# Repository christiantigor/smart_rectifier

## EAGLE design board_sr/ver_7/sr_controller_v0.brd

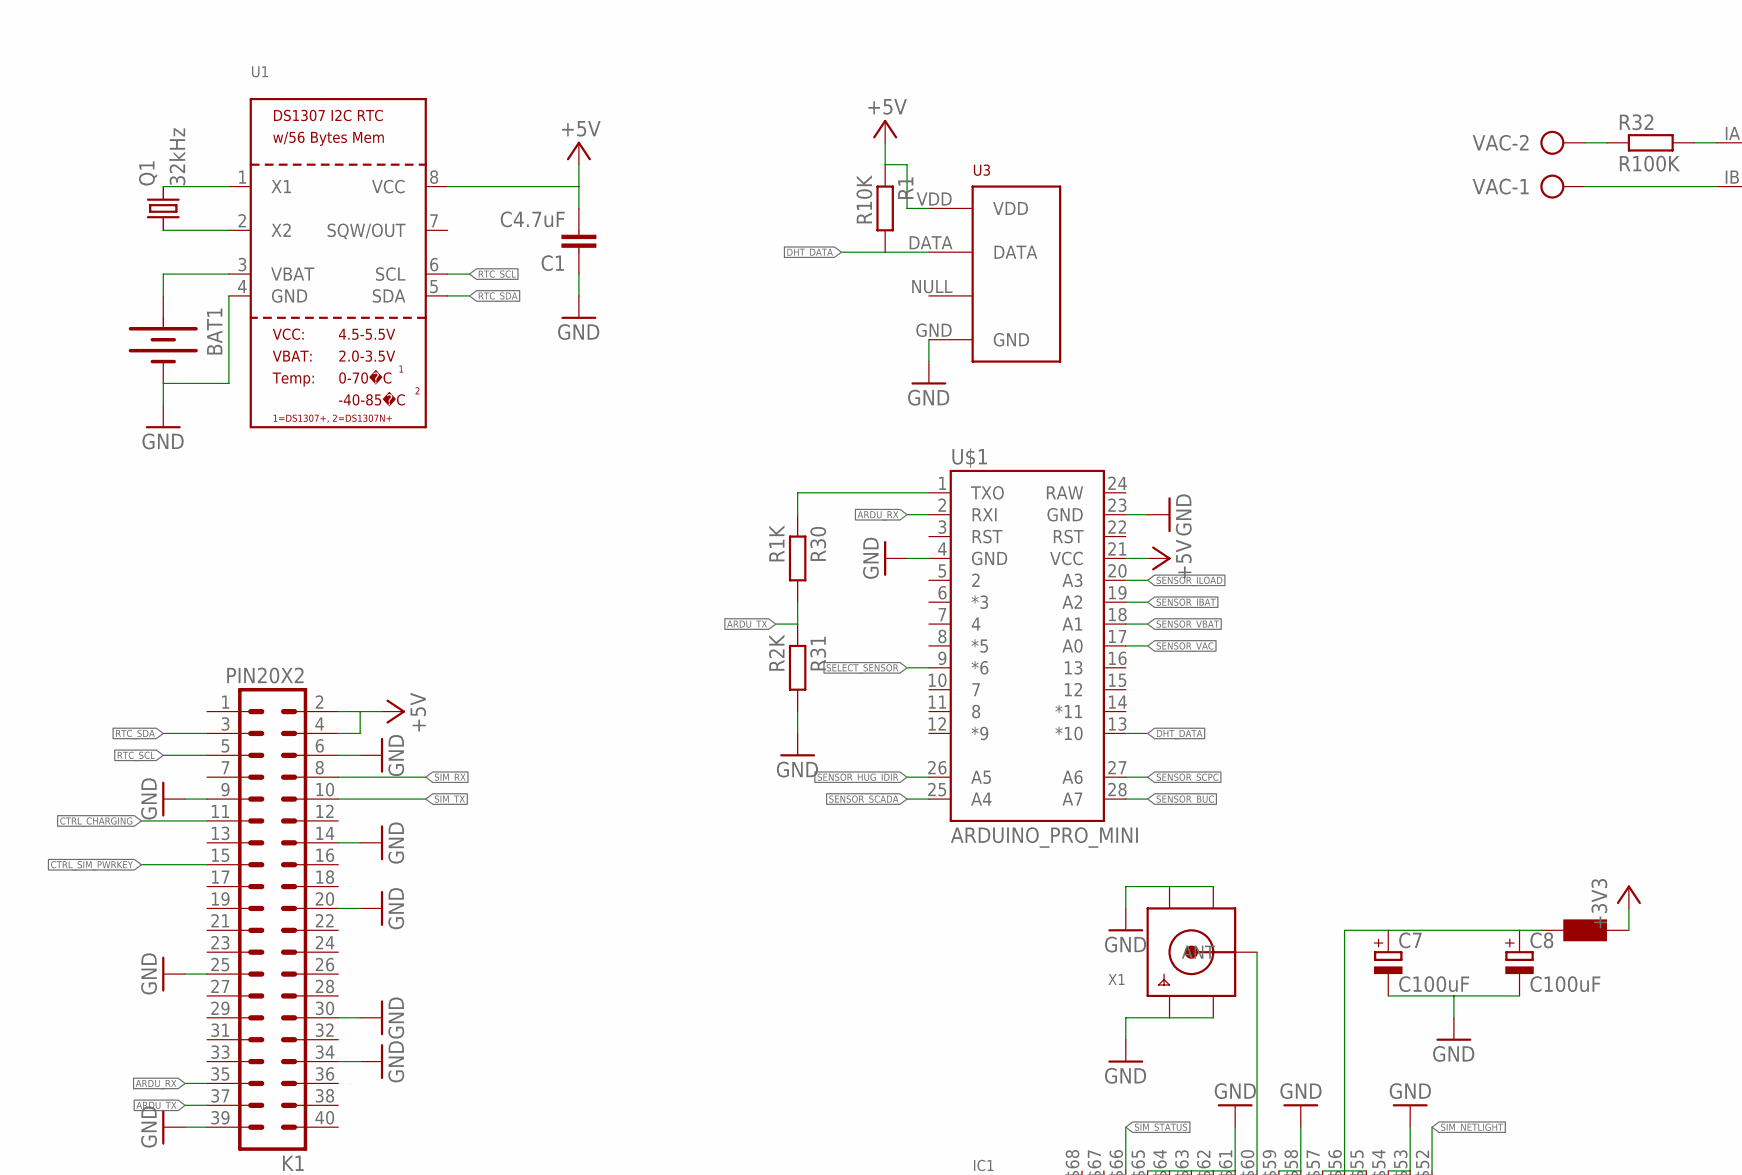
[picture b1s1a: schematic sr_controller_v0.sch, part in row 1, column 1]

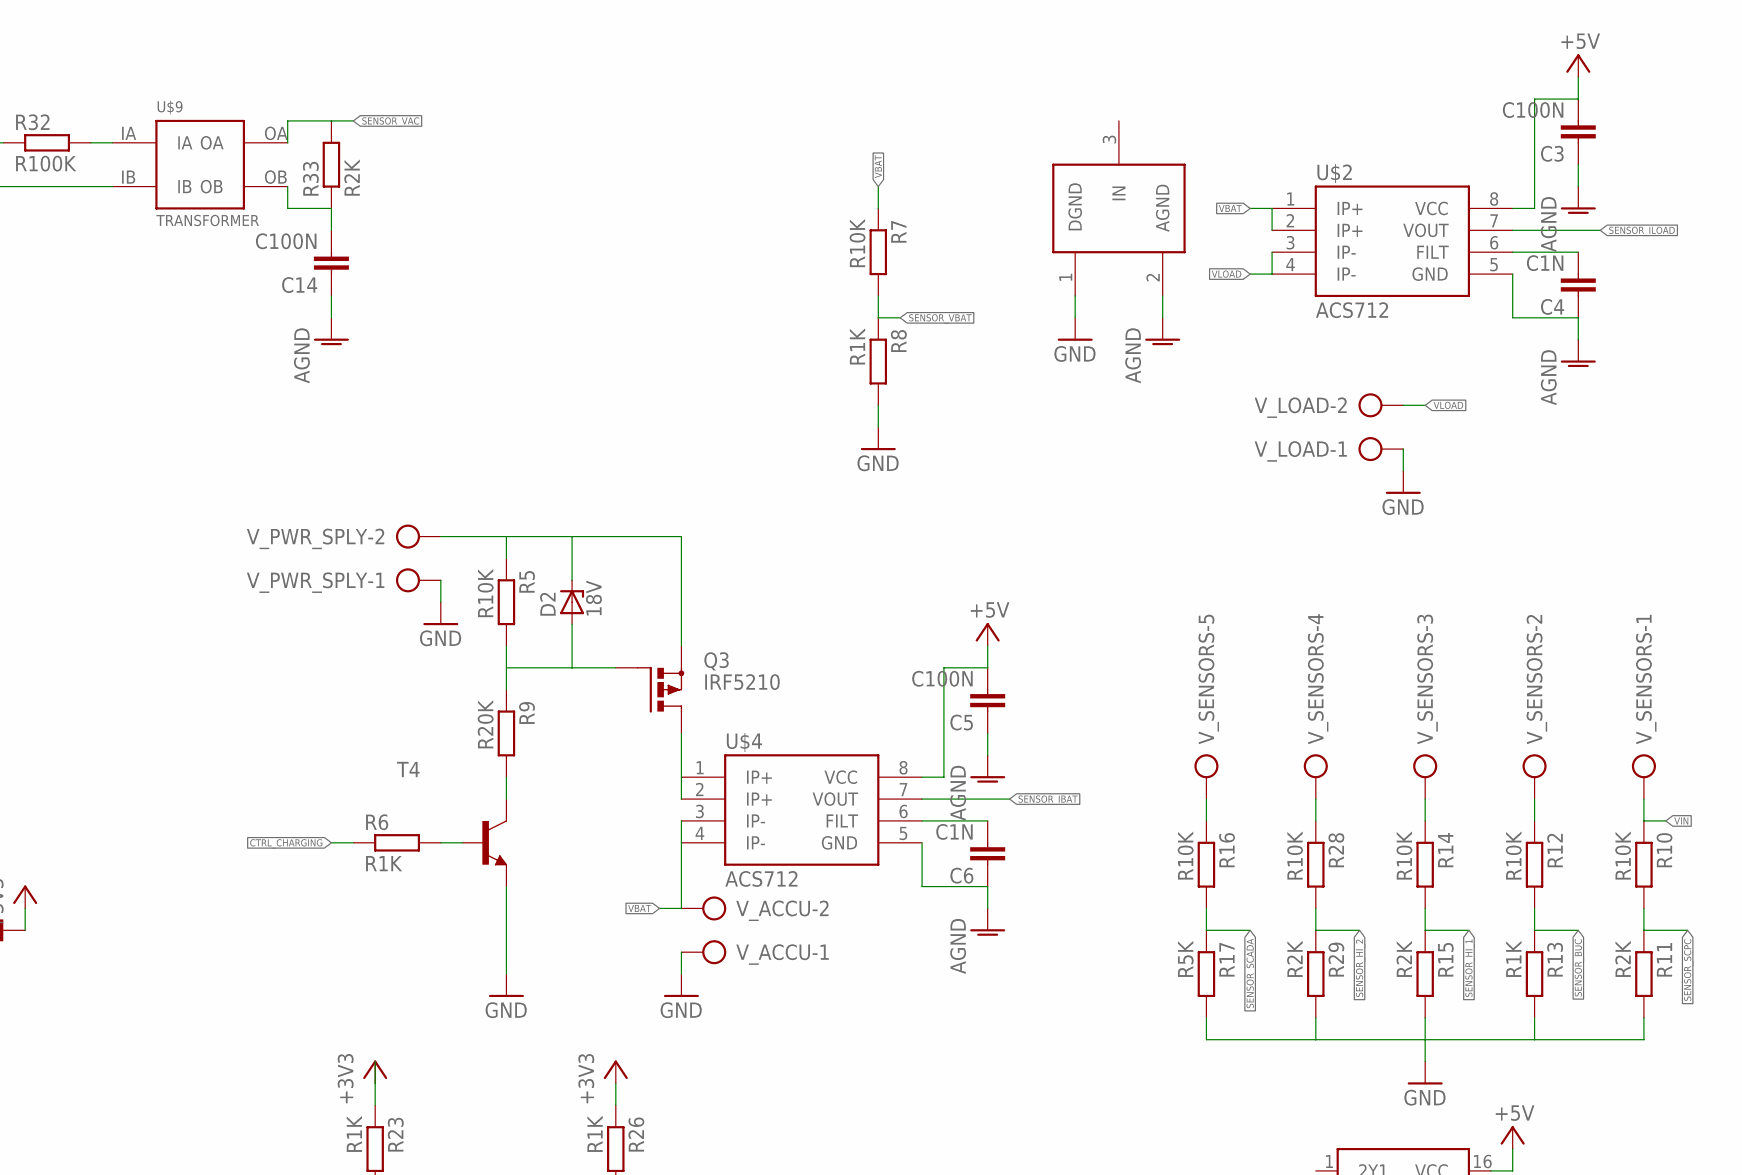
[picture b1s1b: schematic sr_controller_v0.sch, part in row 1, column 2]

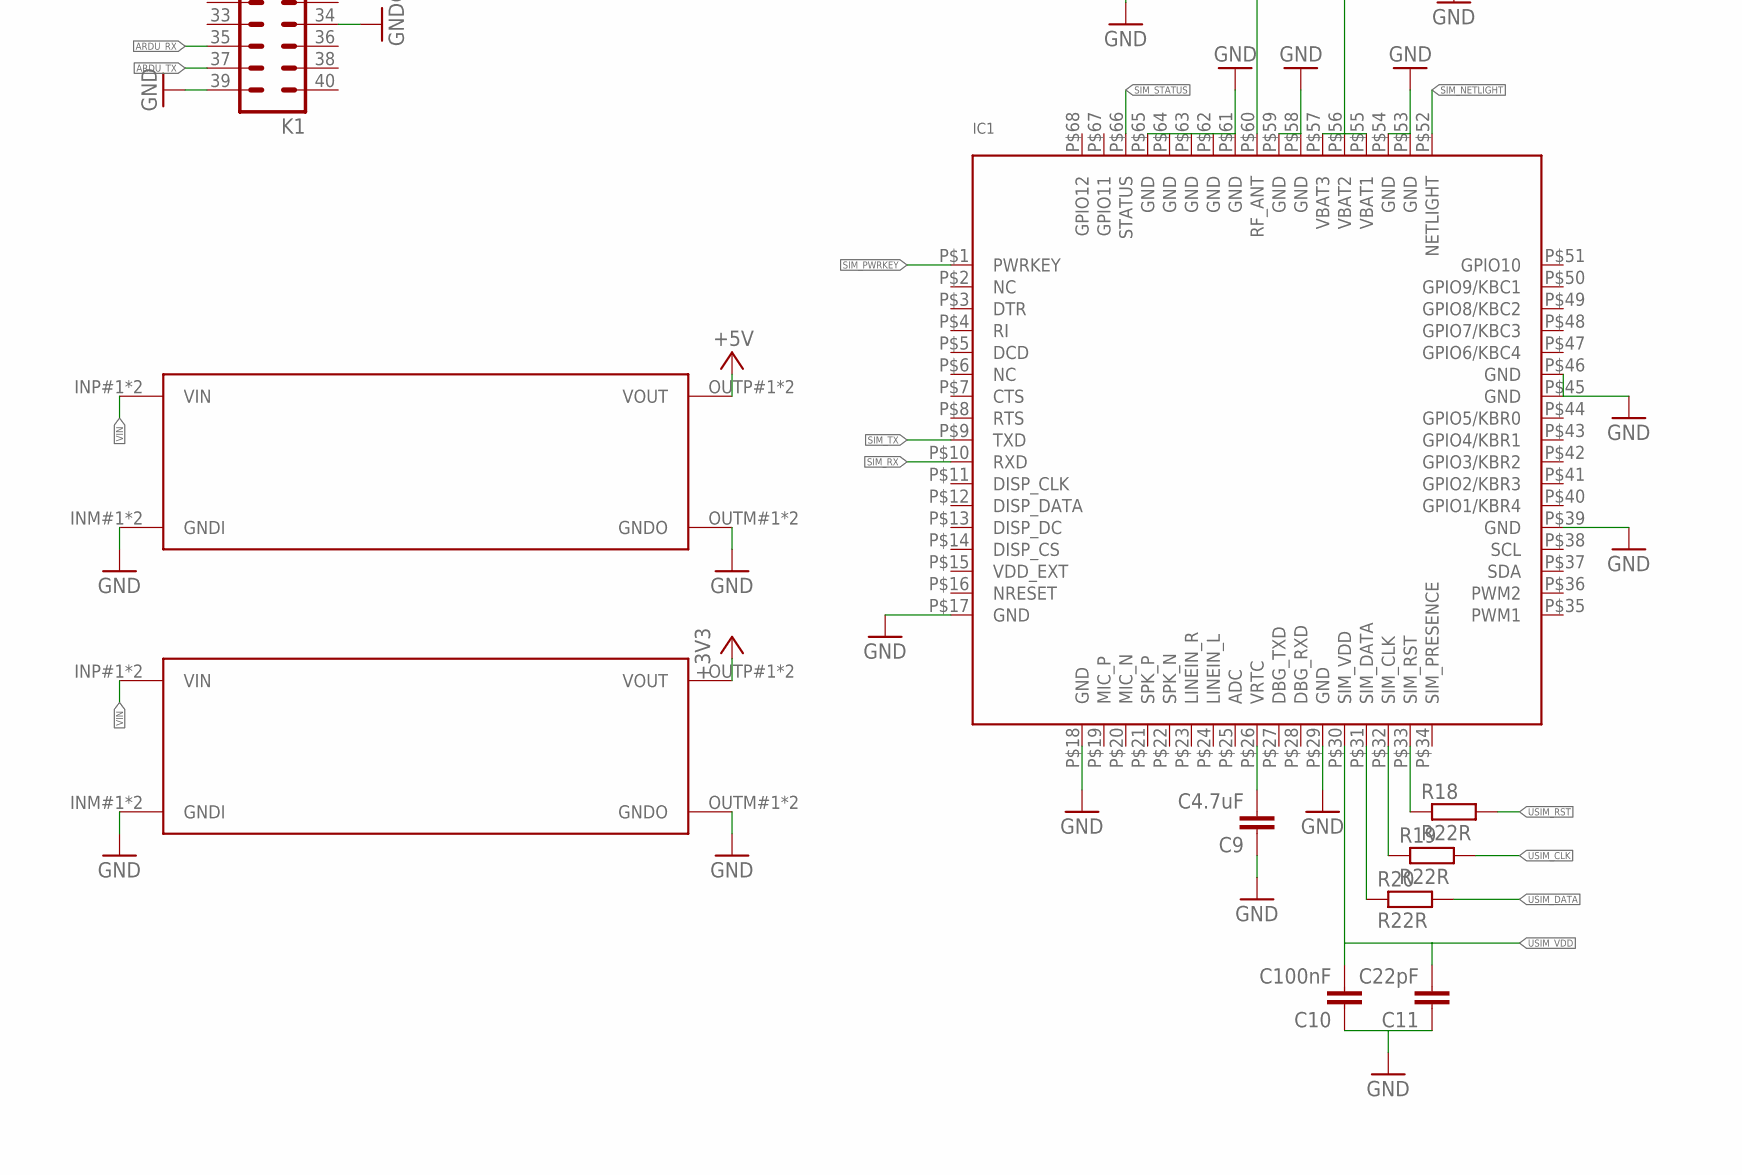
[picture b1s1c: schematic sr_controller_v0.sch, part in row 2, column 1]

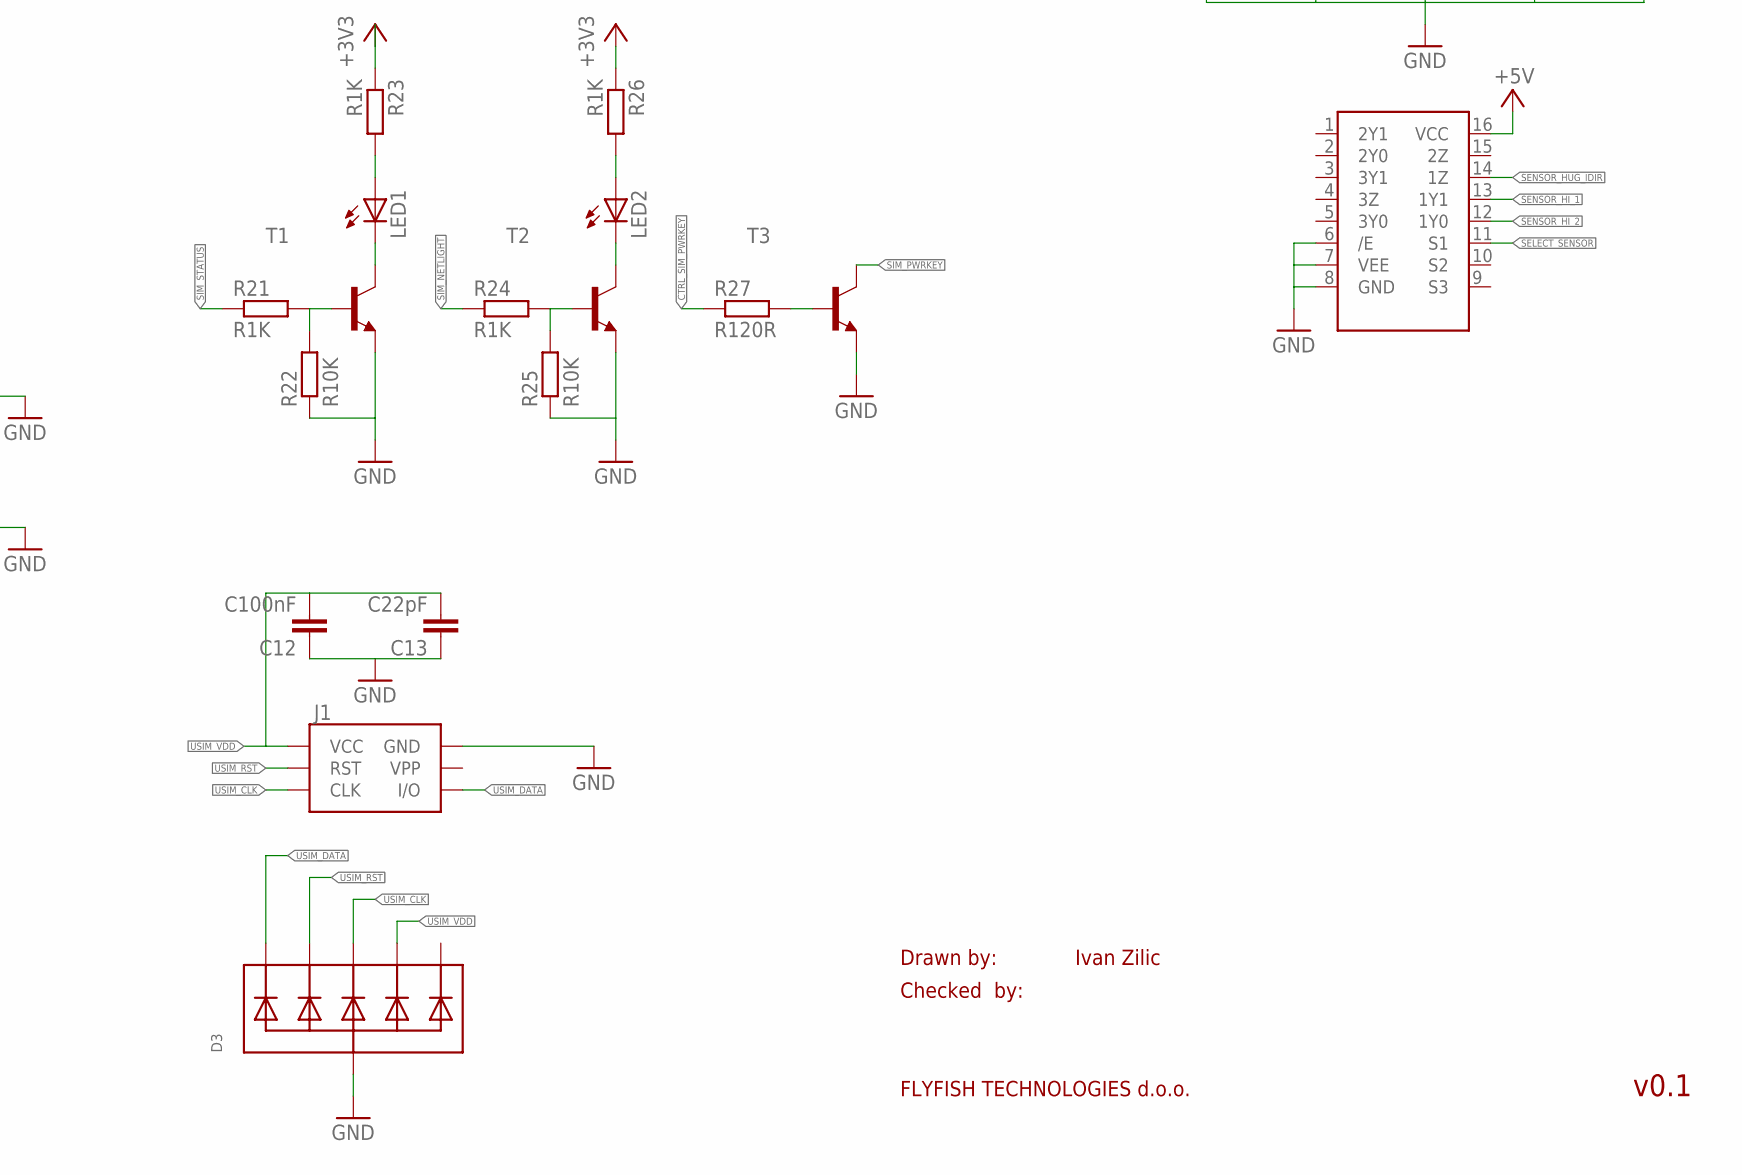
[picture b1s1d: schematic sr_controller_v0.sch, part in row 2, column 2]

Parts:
BAT1: BATTERY20PTH; BATTCOM_20MM_PTH
C1, C9: C4.7uF; C0805
C3, C5, C14: C100N; C0805K
C4, C6: C1N; C0805K
C7, C8: C100uF; 153CLV-0605
C10, C12: C100nF; C0805
C11, C13: C22pF; C0805
D2: 18V; DO41Z10
D3: TVSARRAY_5LANE; SOT363
IC1: GSM_SIM900_LITERAL; SIM900_SMT
J1: SIMHOLDERSIM; SIMHOLDER
K1: PIN20X2; PIN_20X2
LED1, LED2: LEDCHIPLED_0805; CHIPLED_0805
Q1: 32kHz; TC38H
Q3: IRF5210; TO220BV
R1, R5, R7, R10, R12, R14, R16, R22, R25, R28: R10K; R0805
R6, R8, R13, R21, R23, R24, R26, R30: R1K; R0805
R9: R20K; R0805
R11, R15, R29, R31: R2K; R0805
R17: R5K; R0805
R18, R19, R20: R22R; R0805
R27: R120R; R0805
R32: R100K; 0309V
R33: R2K; 0309V
T1, T2, T3, T4: MMBT2222ALT1-NPN-SOT23-BEC; SOT23-BEC
U1: RTC_DS1307; SOIC8_150MIL
U3: RHT03_DHT-22_AM2302; RHT03_DHT-22
U$1: ARDUINO_PRO_MINI
U$2, U$4: ACS712; SO08
U$3: GND_CONNECT
U$5: FB0603; L0603
U$6, U$7: DCDCMODULE_SMALL; DCDCMODULE-SMALL
U$8: 74HC4053D; SO16
U$9: TRANSFORMER; TV16
VAC: AK300/2
V_ACCU: AK300/2
V_LOAD: AK300/2
V_PWR_SPLY: AK300/2
V_SENSORS: AK300/5
X1: SMACONNECTOR; SMA90_DIP

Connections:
+3V3: R23.1, R26.1, U$5.2, U$7.OUTP#1 (VOUT), U$7.OUTP#2 (VOUT)
+5V: C1.2, C3.2, C5.2, K1.2, K1.4, R1.1, U1.8 (VCC), U3.VDD, U$1.21 (VCC), U$2.8 (VCC), U$4.8 (VCC), U$6.OUTP#1 (VOUT), U$6.OUTP#2 (VOUT), U$8.16 (VCC)
AGND: C3.1, C4.1, C5.1, C6.1, C14.1, U$2.5 (GND), U$3.2 (AGND), U$4.5 (GND)
ARDU_RX: K1.35, U$1.2 (RXI)
ARDU_TX: K1.37, R30.2, R31.1
CTRL_CHARGING: K1.11, R6.1
CTRL_SIM_PWRKEY: K1.15, R27.1
DHT_DATA: R1.2, U3.DATA, U$1.13 (*10)
GND: BAT1.2 (-), C1.1, C7.-, C8.-, C9.1, C10.1, C11.1, C12.1, C13.1, D3.2 (A), IC1.P$17 (GND), IC1.P$18 (GND), IC1.P$29 (GND), IC1.P$39 (GND), IC1.P$45 (GND), IC1.P$46 (GND), IC1.P$53 (GND), IC1.P$54 (GND), IC1.P$58 (GND), IC1.P$59 (GND), IC1.P$61 (GND), IC1.P$62 (GND), IC1.P$63 (GND), IC1.P$64 (GND), IC1.P$65 (GND), J1.C5 (GND), K1.6, K1.9, K1.14, K1.20, K1.25, K1.30, K1.34, K1.39, R8.2, R11.2, R13.2, R15.2, R17.2, R22.1, R25.1, R29.2, R31.2, T1.E, T2.E, T3.E, T4.E, U1.4 (GND), U3.GND, U$1.4 (GND), U$1.23 (GND), U$3.1 (DGND), U$6.INM#1 (GNDI), U$6.INM#2 (GNDI), U$6.OUTM#1 (GNDO), U$6.OUTM#2 (GNDO), U$7.INM#1 (GNDI), U$7.INM#2 (GNDI), U$7.OUTM#1 (GNDO), U$7.OUTM#2 (GNDO), U$8.6 (/E), U$8.7 (VEE), U$8.8 (GND), V_ACCU.1, V_LOAD.1, V_PWR_SPLY.1, X1.GND1, X1.GND2, X1.GND3, X1.GND4
GPIO11: IC1.P$67 (GPIO11)
GPIO12: IC1.P$68 (GPIO12)
unnamed: R32.1, VAC.2
unnamed: U$9.IB, VAC.1
unnamed: Q1.2, U1.1 (X1)
unnamed: Q1.1, U1.2 (X2)
unnamed: BAT1.1 (+), U1.3 (VBAT)
unnamed: R12.1, V_SENSORS.2
unnamed: C4.2, U$2.6 (FILT)
unnamed: D2.A, Q3.G, R5.2, R9.1
unnamed: D2.C, Q3.S, R5.1, V_PWR_SPLY.2
unnamed: R6.2, T4.B
unnamed: R9.2, T4.C
unnamed: Q3.D, U$4.1 (IP+), U$4.2 (IP+)
unnamed: C6.2, U$4.6 (FILT)
unnamed: R14.1, V_SENSORS.3
unnamed: R28.1, V_SENSORS.4
unnamed: R16.1, V_SENSORS.5
unnamed: IC1.P$60 (RF_ANT), X1.ANTENNA (ANT)
unnamed: C7.+, C8.+, IC1.P$55 (VBAT1), IC1.P$56 (VBAT2), IC1.P$57 (VBAT3), U$5.1
unnamed: C9.2, IC1.P$26 (VRTC)
unnamed: IC1.P$33 (SIM_RST), R18.1
unnamed: IC1.P$32 (SIM_CLK), R19.1
unnamed: IC1.P$31 (SIM_DATA), R20.1
unnamed: LED1.C, T1.C
unnamed: LED1.A, R23.2
unnamed: LED2.C, T2.C
unnamed: R21.2, R22.2, T1.B
unnamed: LED2.A, R26.2
unnamed: R24.2, R25.2, T2.B
unnamed: R27.2, T3.B
unnamed: R30.1, U$1.1 (TXO)
unnamed: R32.2, U$9.IA
unnamed: C14.2, R33.1, U$9.OB
RTC_SCL: K1.5, U1.6 (SCL)
RTC_SDA: K1.3, U1.5 (SDA)
SELECT_SENSOR: U$1.9 (*6), U$8.11 (S1)
SENSOR_BUC: R12.2, R13.1, U$1.28 (A7)
SENSOR_HI_1: R14.2, R15.1, U$8.13 (1Y1)
SENSOR_HI_2: R28.2, R29.1, U$8.12 (1Y0)
SENSOR_HUG_IDIR: U$1.26 (A5), U$8.14 (1Z)
SENSOR_IBAT: U$1.19 (A2), U$4.7 (VOUT)
SENSOR_ILOAD: U$1.20 (A3), U$2.7 (VOUT)
SENSOR_SCADA: R16.2, R17.1, U$1.25 (A4)
SENSOR_SCPC: R10.2, R11.1, U$1.27 (A6)
SENSOR_VAC: R33.2, U$1.17 (A0), U$9.OA
SENSOR_VBAT: R7.2, R8.1, U$1.18 (A1)
SIM_NETLIGHT: IC1.P$52 (NETLIGHT), R24.1
SIM_PWRKEY: IC1.P$1 (PWRKEY), T3.C
SIM_RX: IC1.P$10 (RXD), K1.8
SIM_STATUS: IC1.P$66 (STATUS), R21.1
SIM_TX: IC1.P$9 (TXD), K1.10
USIM_CLK: D3.4 (C3), J1.C3 (CLK), R19.2
USIM_DATA: D3.1 (C1), J1.C7 (I/O), R20.2
USIM_RST: D3.3 (C2), J1.C2 (RST), R18.2
USIM_VDD: C10.2, C11.2, C12.2, C13.2, D3.5 (C4), IC1.P$30 (SIM_VDD), J1.C1 (VCC)
VBAT: R7.1, U$2.1 (IP+), U$2.2 (IP+), U$4.3 (IP-), U$4.4 (IP-), V_ACCU.2
VIN: R10.1, U$6.INP#1 (VIN), U$6.INP#2 (VIN), U$7.INP#1 (VIN), U$7.INP#2 (VIN), V_SENSORS.1
VLOAD: U$2.3 (IP-), U$2.4 (IP-), V_LOAD.2

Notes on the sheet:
Drawn by:
Checked by:
FLYFISH TECHNOLOGIES d.o.o.
Ivan Zilic
v0.1

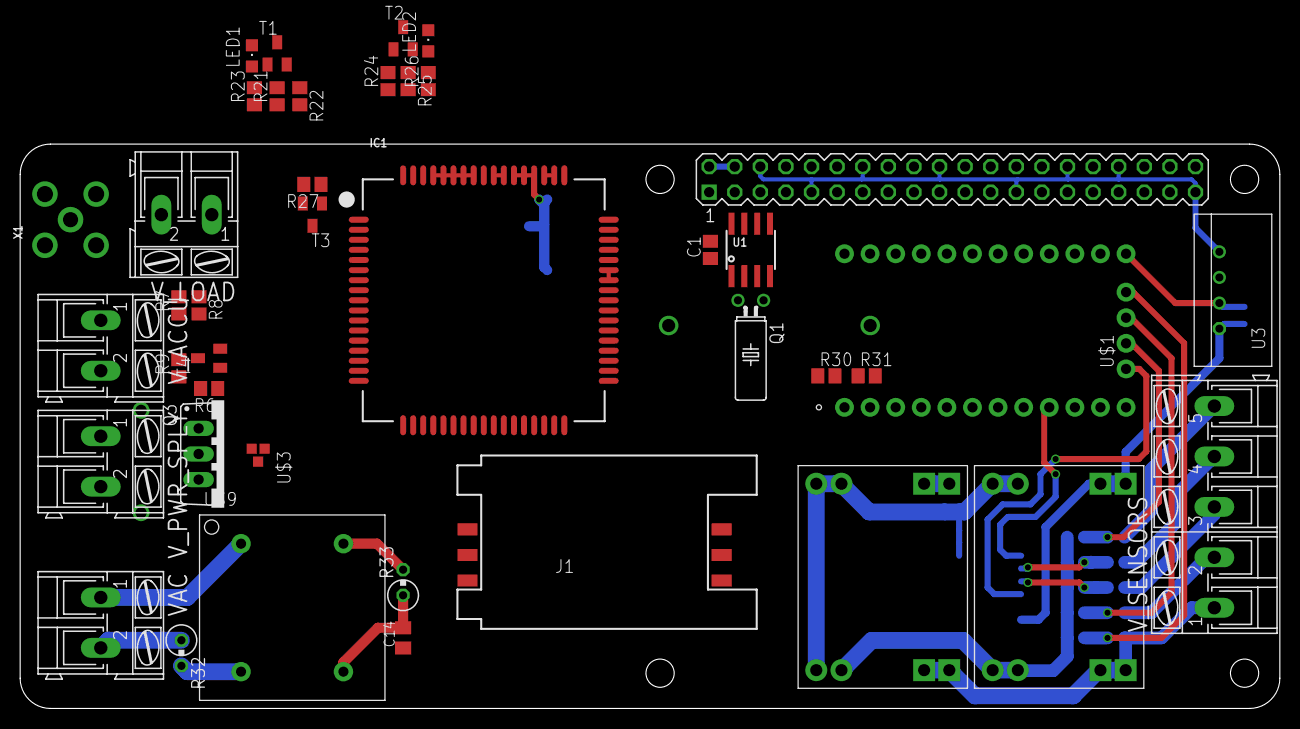
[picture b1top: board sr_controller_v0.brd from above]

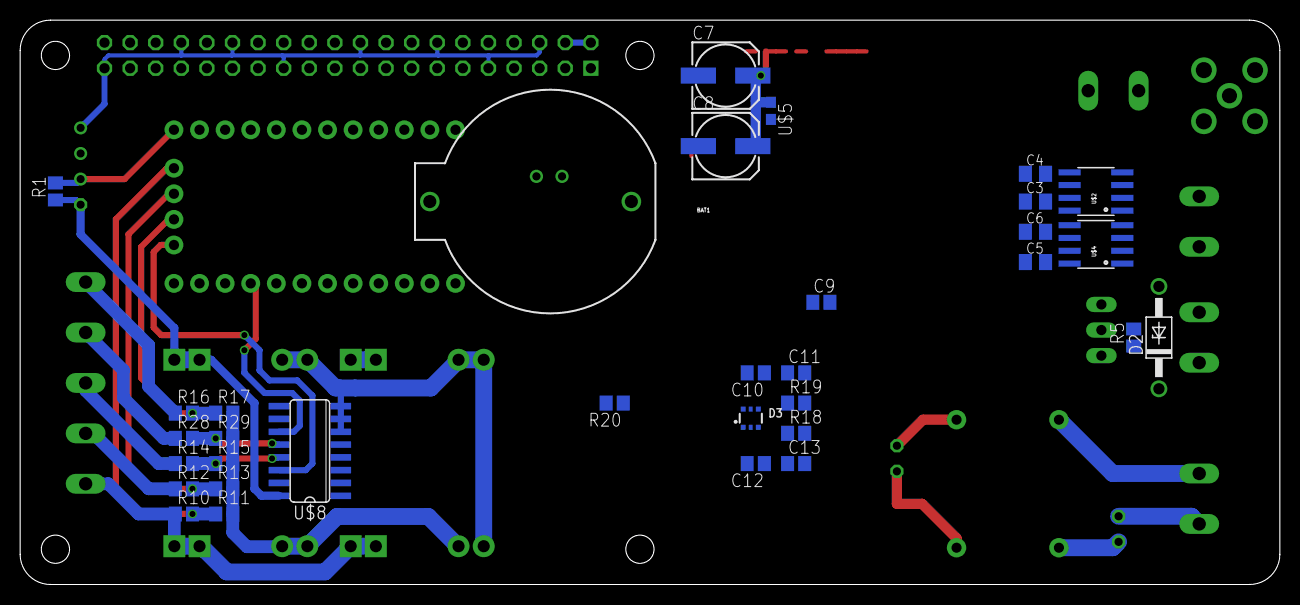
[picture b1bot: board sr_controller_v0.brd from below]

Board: 2 copper layers, 125.0 x 56.0 mm, 74 parts (33 on the bottom side), 66 nets.

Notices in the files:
parts and their libraries:
microbuilder: This work is placed in the public domain, and may be freely used for commercial and non-commercial work with the following conditions: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
SparkFun-Electromechanical: Licensing: Creative Commons ShareAlike 4.0 International - https://creativecommons.org/licenses/by-sa/4.0
